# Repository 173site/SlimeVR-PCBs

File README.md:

# SlimeVR-PCBs

Includes CAD files for the PCBs using JST six pin connectors for the extensions

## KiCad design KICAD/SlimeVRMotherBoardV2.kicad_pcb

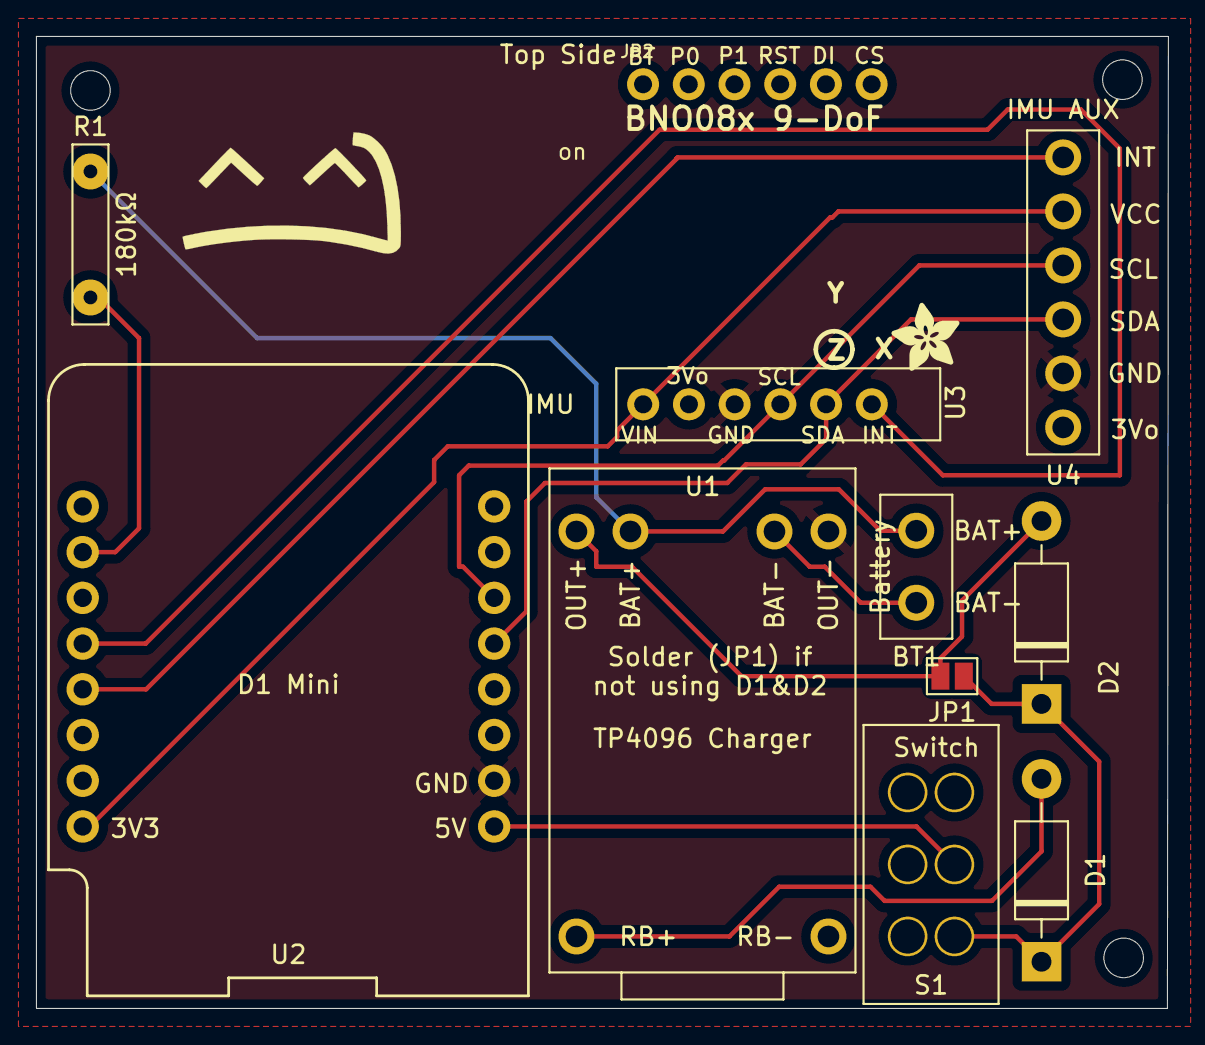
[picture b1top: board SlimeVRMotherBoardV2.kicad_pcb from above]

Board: 2 copper layers, 62.9 x 54.0 mm, 12 parts (0 on the bottom side), 13 nets.

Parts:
BT1: Battery
D1, D2: 1N5817; D_DO-41_SOD81_P10.16mm_Horizontal
JP1: SolderJumper_2_Open; SolderJumper-2_P1.3mm_Open_Pad1.0x1.5mm
JP2: 1X06_ROUND_70
R1: R180Ω; 180KΩ
S1: SlideSwitch; SS22F32
U1: 4056Board
U2: WeMos_D1_mini; wemos-d1-mini-connectors-only
U3, U4: BN008X; BNO080_Connector
U$22: ADAFRUIT_3.5MM

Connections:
unnamed: BT1.1 (Bat-), U1.3 (Battery-)
unnamed: BT1.2 (Bat+), R1.1, U1.2 (Battery+)
unnamed: D1.1 (K), D2.1 (K), JP1.2 (B), S1.1 (T1)
unnamed: D1.2 (A), U1.5 (RB+)
unnamed: D2.2 (A), JP1.1 (A), U1.1 (Out+)
unnamed: R1.2, U2.2 (A0)
unnamed: S1.2 (T2), U2.9 (5V)
unnamed: U1.4 (Out-), U2.10 (GND), U3.2 (GND), U4.2 (GND)
unnamed: U2.4 (D5), U3.6 (INT)
unnamed: U2.5 (D6), U4.6 (INT)
unnamed: U2.8 (3.3V), U3.1 (VCC), U4.1 (VCC)
unnamed: U2.13 (D2), U3.4 (SDA), U4.4 (SDA)
unnamed: U2.14 (D1), U3.3 (SCL), U4.3 (SCL)

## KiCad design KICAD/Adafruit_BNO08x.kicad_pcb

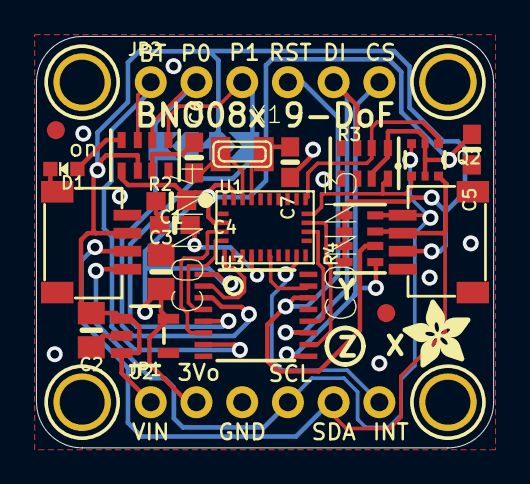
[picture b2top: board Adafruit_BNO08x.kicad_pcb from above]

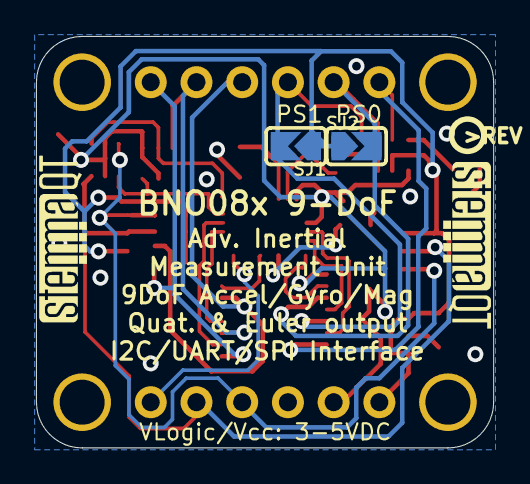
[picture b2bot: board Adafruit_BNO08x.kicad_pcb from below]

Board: 2 copper layers, 25.4 x 22.9 mm, 32 parts (5 on the bottom side), 24 nets.

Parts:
C1, C4, C5: 0.1uF; 0603-NO
C2, C3: 10uF; 0805-NO
C6, C7: 22pF; 0603-NO
CONN3, CONN4: STEMMA_I2C_QT; JST_SH4
D1: GREEN; CHIPLED_0603_NOOUTLINE
FID3, FID4: FIDUCIAL_1MM
JP1, JP2: 1X06_ROUND_70
Q2: BSS138; SOT363
R2, R3, R4: 10K; RESPACK_4X0603
SJ1: PS1; SOLDERJUMPER_ARROW_NOPASTE
SJ2: PS0; SOLDERJUMPER_ARROW_NOPASTE
U1: BNO080
U2: AP2112K-3.3; SOT23-5
U3: 74AHC4050; TSSOP16
U$1, U$17, U$19, U$21: MOUNTINGHOLE2.5; MOUNTINGHOLE_2.5_PLATED
U$22: ADAFRUIT_3.5MM
U$25: PCBFEAT-REV-040
U$30, U$31: STEMMAQT
X1: 32.768; XTAL3215

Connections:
3.3V: C1.1, C3.1, C5.1, JP1.2, Q2.2, Q2.5, R2.5, R3.3, R3.5, U1.3, U1.28, U2.5, U3.1
BOOT: JP2.1, R2.3, U3.7
BOOT_3V: U1.4, U3.6
CAP: C4.2, U1.9
CS: JP2.6, R4.1, U3.9
CS_3V: U1.18, U3.10
GND: C1.2, C2.2, C3.2, C4.1, C5.2, C6.2, C7.2, CONN3.1, CONN3.MT1, CONN3.MT2, CONN4.1, CONN4.MT1, CONN4.MT2, D1.C, JP1.3, R2.7, R2.8, R3.1, R3.2, R3.8, U1.2, U1.10, U1.25, U2.2, U3.8
INT: JP1.6, U1.14
MOSI: JP2.5, R3.7, U3.11
MOSI_3V: U1.17, U3.12
unnamed: D1.A, R2.4
PS0: JP2.2, R2.2, SJ2.2, U3.3
PS0_3V: U1.6, U3.2
PS1: JP2.3, R2.1, SJ1.2, U3.5
PS1_3V: U1.5, U3.4
RST: JP2.4, R4.2, U3.14
RST_3V: U1.11, U3.15
SCL/SCK/RX: CONN3.4, CONN4.4, JP1.4, Q2.6, R4.4
SCL_3V: Q2.1, R3.4, U1.19
SDA/MISO/TX: CONN3.3, CONN4.3, JP1.5, Q2.3, R4.3
SDA_3V: Q2.4, R3.6, U1.20
VCC: C2.1, CONN3.2, CONN4.2, JP1.1, R2.6, R4.5, R4.6, R4.7, R4.8, SJ1.1, SJ2.1, U2.1, U2.3
XIN: C6.1, U1.27, X1.P$1
XOUT: C7.1, U1.26, X1.P$2

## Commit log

2023-02-04 Create kicad
2023-02-04 Create gerber

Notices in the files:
KICAD/SlimeVRMotherBoardV2.kicad_pcb:
creativecommons.org/licenses/by/4.0
License: CC BY 4.0
